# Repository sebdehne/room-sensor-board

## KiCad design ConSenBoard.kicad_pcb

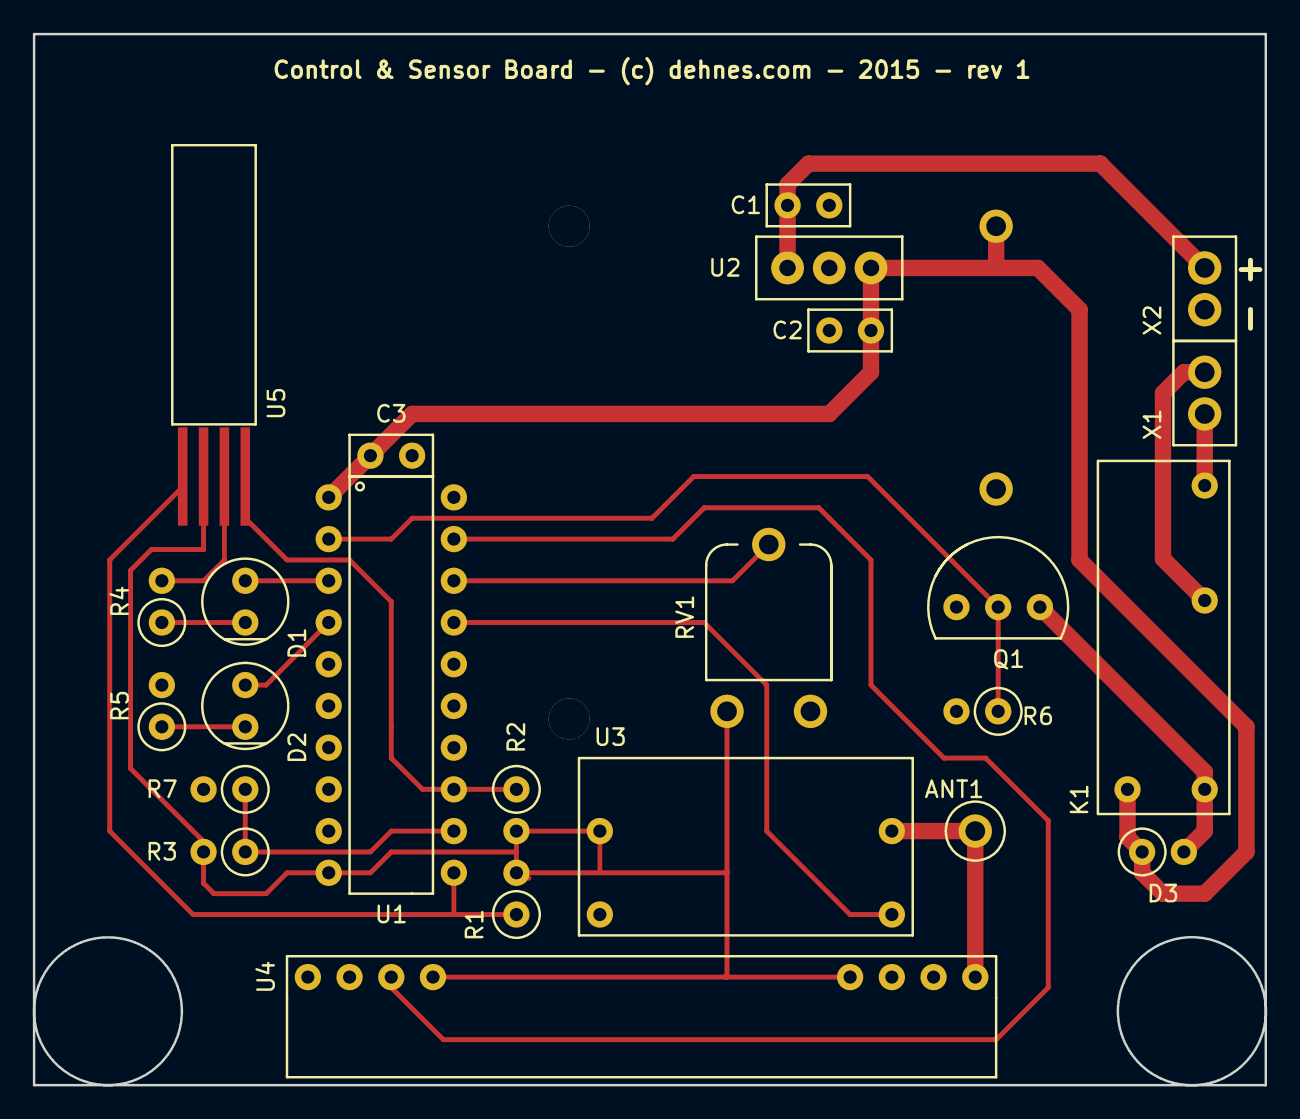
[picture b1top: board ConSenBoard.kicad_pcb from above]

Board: 2 copper layers, 75.0 x 64.0 mm, 25 parts (1 on the bottom side), 19 nets.

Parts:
ANT1: Antenna
BT1: 3x AAA; Battery-3xAAA
C1: 0.33µF; Cap-DIP-2
C2, C3: 0.1µF; Cap-DIP-2
D1, D2: LED; LED_5mm
D3: 1N4007-T; Resistor_vertical_100mil
K1: Relay_NO; Omron-GSNB-1A
Q1: 2N7000GOS-ND; TO-92_MOSFET
R1, R2: 2.2kΩ; Resistor_vertical_100mil
R3, R4, R5: Resistor_vertical_100mil
R6: 10kΩ; Resistor_vertical_100mil
R7: LightSensor; Resistor_vertical_100mil
RV1: 10K; Potensiometer
U1: PIC16F690-I/P-ND; PIC16F690-DIP
U2: LM7805CT; L78M05-TO-220
U3: AM-RT4-433; RT4-433
U4: RX433N
U5: ChipCap2-SIP
X1, X2: TERM; TerminalBlock_2

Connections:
GND: BT1.2, C1.2, C2.2, C3.2, Q1.1, R4.2, R5.2, R6.2, R7.2, RV1.3, U1.20, U2.2, U3.2, U4.1, U4.6, U4.7, U5.3, X2.1
I2C_SCL: R1.1, U1.11, U5.1
I2C_SDA: R2.1, U1.13, U5.4
LED1: D1.2, U1.3
LED2: D2.2, U1.4
unnamed: ANT1.1, U3.4, U4.8
unnamed: C1.1, U2.1, X2.2
unnamed: D1.1, R4.1
unnamed: D2.1, R5.1
unnamed: D3.2, K1.1, Q1.3
unnamed: K1.3, X1.1
unnamed: K1.4, X1.2
RX-signal: U1.19, U4.3
RX-signal-ref: RV1.2, U1.18
Relay: Q1.2, R6.1, U1.2
Sensor: R3.1, R7.1, U1.12
Switched_PW_20mA: R1.2, R2.2, R3.2, RV1.1, U1.10, U3.1, U4.4, U4.5, U5.2
TX-signal: U1.17, U3.3
Vdd5V: BT1.1, C2.1, C3.1, D3.1, K1.2, U1.1, U2.3

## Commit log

2016-11-20 init commit
